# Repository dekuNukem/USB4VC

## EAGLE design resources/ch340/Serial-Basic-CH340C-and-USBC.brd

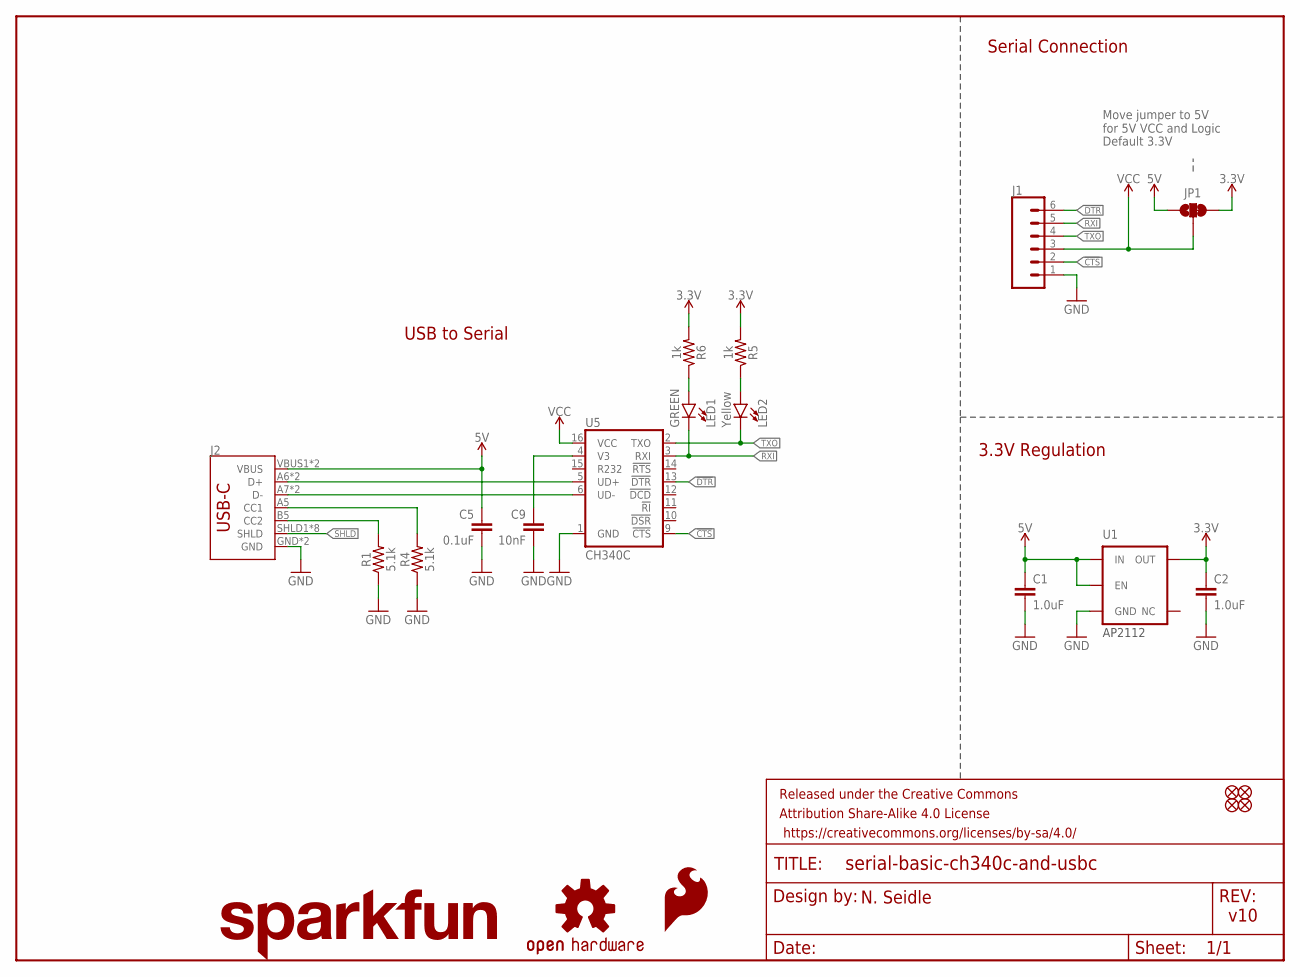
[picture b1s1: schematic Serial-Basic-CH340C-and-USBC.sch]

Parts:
C1, C2: 1.0uF; 0603
C5: 0.1uF; 0603
C9: 10nF; 0603
FRAME1: FRAME-LETTER; CREATIVE_COMMONS
J1: CONN_06SMD-FEMALE-V2; 1X06-SMD-FEMALE
J2: USB_C16PIN; USB-C-16P
JP1: JUMPER-SMT_3_1-NC_TRACE_SILK; SMT-JUMPER_3_1-NC_TRACE_SILK
JP3, JP4, JP5, JP6: FIDUCIAL1X2; FIDUCIAL-1X2
LED1: GREEN; LED-0603
LED2: Yellow; LED-0603
LOGO1: OSHW-LOGOS; OSHW-LOGO-S
LOGO2: SFE_LOGO_FLAME.1_INCH; SFE_LOGO_FLAME_.1
LOGO3: SFE_LOGO_NAME.1_INCH; SFE_LOGO_NAME_.1
R1, R4: 5.1k; 0603
R5, R6: 1k; 0603
U1: 3.3V; SOT23-5
U5: CH340C; SO016

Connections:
3.3V: C2.1, JP1.3, R5.2, R6.2, U1.5 (OUT)
5V: C1.1, C5.1, J2.VBUS1 (VBUS), J2.VBUS2 (VBUS), JP1.1, U1.1 (IN), U1.3 (EN)
!CTS: J1.2, U5.9 (!CTS)
!DTR: J1.6, U5.13 (!DTR)
CC1: J2.A5 (CC1), R4.2
CC2: J2.B5 (CC2), R1.2
D+: J2.A6 (D+), J2.B6 (D+), U5.5 (UD+)
D-: J2.A7 (D-), J2.B7 (D-), U5.6 (UD-)
GND: C1.2, C2.2, C5.2, C9.2, J1.1, J2.GND, J2.GND2 (GND), R1.1, R4.1, U1.2 (GND), U5.1 (GND)
unnamed: C9.1, U5.4 (V3)
unnamed: LED1.A, R6.1
unnamed: LED2.A, R5.1
RXI: J1.5, LED1.C, U5.3 (RXI)
SHLD: J2.SHLD1 (SHLD), J2.SHLD2 (SHLD), J2.SHLD3 (SHLD), J2.SHLD4 (SHLD), J2.SHLD5 (SHLD), J2.SHLD6 (SHLD), J2.SHLD7 (SHLD), J2.SHLD8 (SHLD)
TXO: J1.4, LED2.C, U5.2 (TXO)
VCC: J1.3, JP1.2, U5.16 (VCC)

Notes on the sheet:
Default 3.3V
v10
USB to Serial
3.3V Regulation
N. Seidle
Move jumper to 5V for 5V VCC and Logic
Serial Connection
AP2112

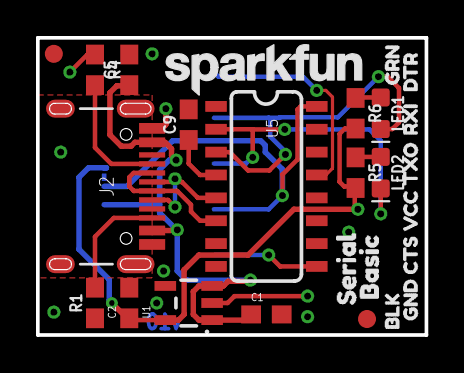
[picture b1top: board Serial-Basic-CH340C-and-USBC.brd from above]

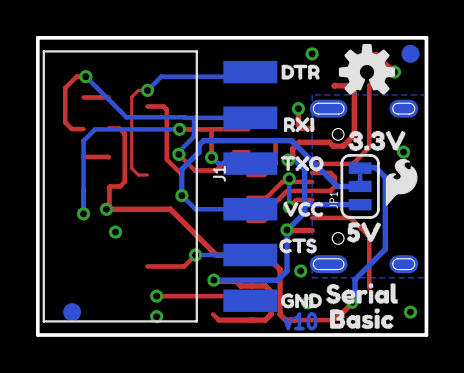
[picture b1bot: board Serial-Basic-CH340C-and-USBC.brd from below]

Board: 2 copper layers, 21.6 x 16.5 mm, 43 parts (16 on the bottom side), 16 nets.

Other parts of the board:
U$1, U$14: CTS1
U$2: 3#3V8
U$3: 5V9
U$4, U$9: SERIAL0
U$5, U$12: TXO0
U$6, U$13: VCC2
U$7, U$11: BASIC1
U$8, U$18: DTR0
U$10, U$21: RXI1
U$15, U$19: GND5
U$17: BLK6
U$20: GRN7

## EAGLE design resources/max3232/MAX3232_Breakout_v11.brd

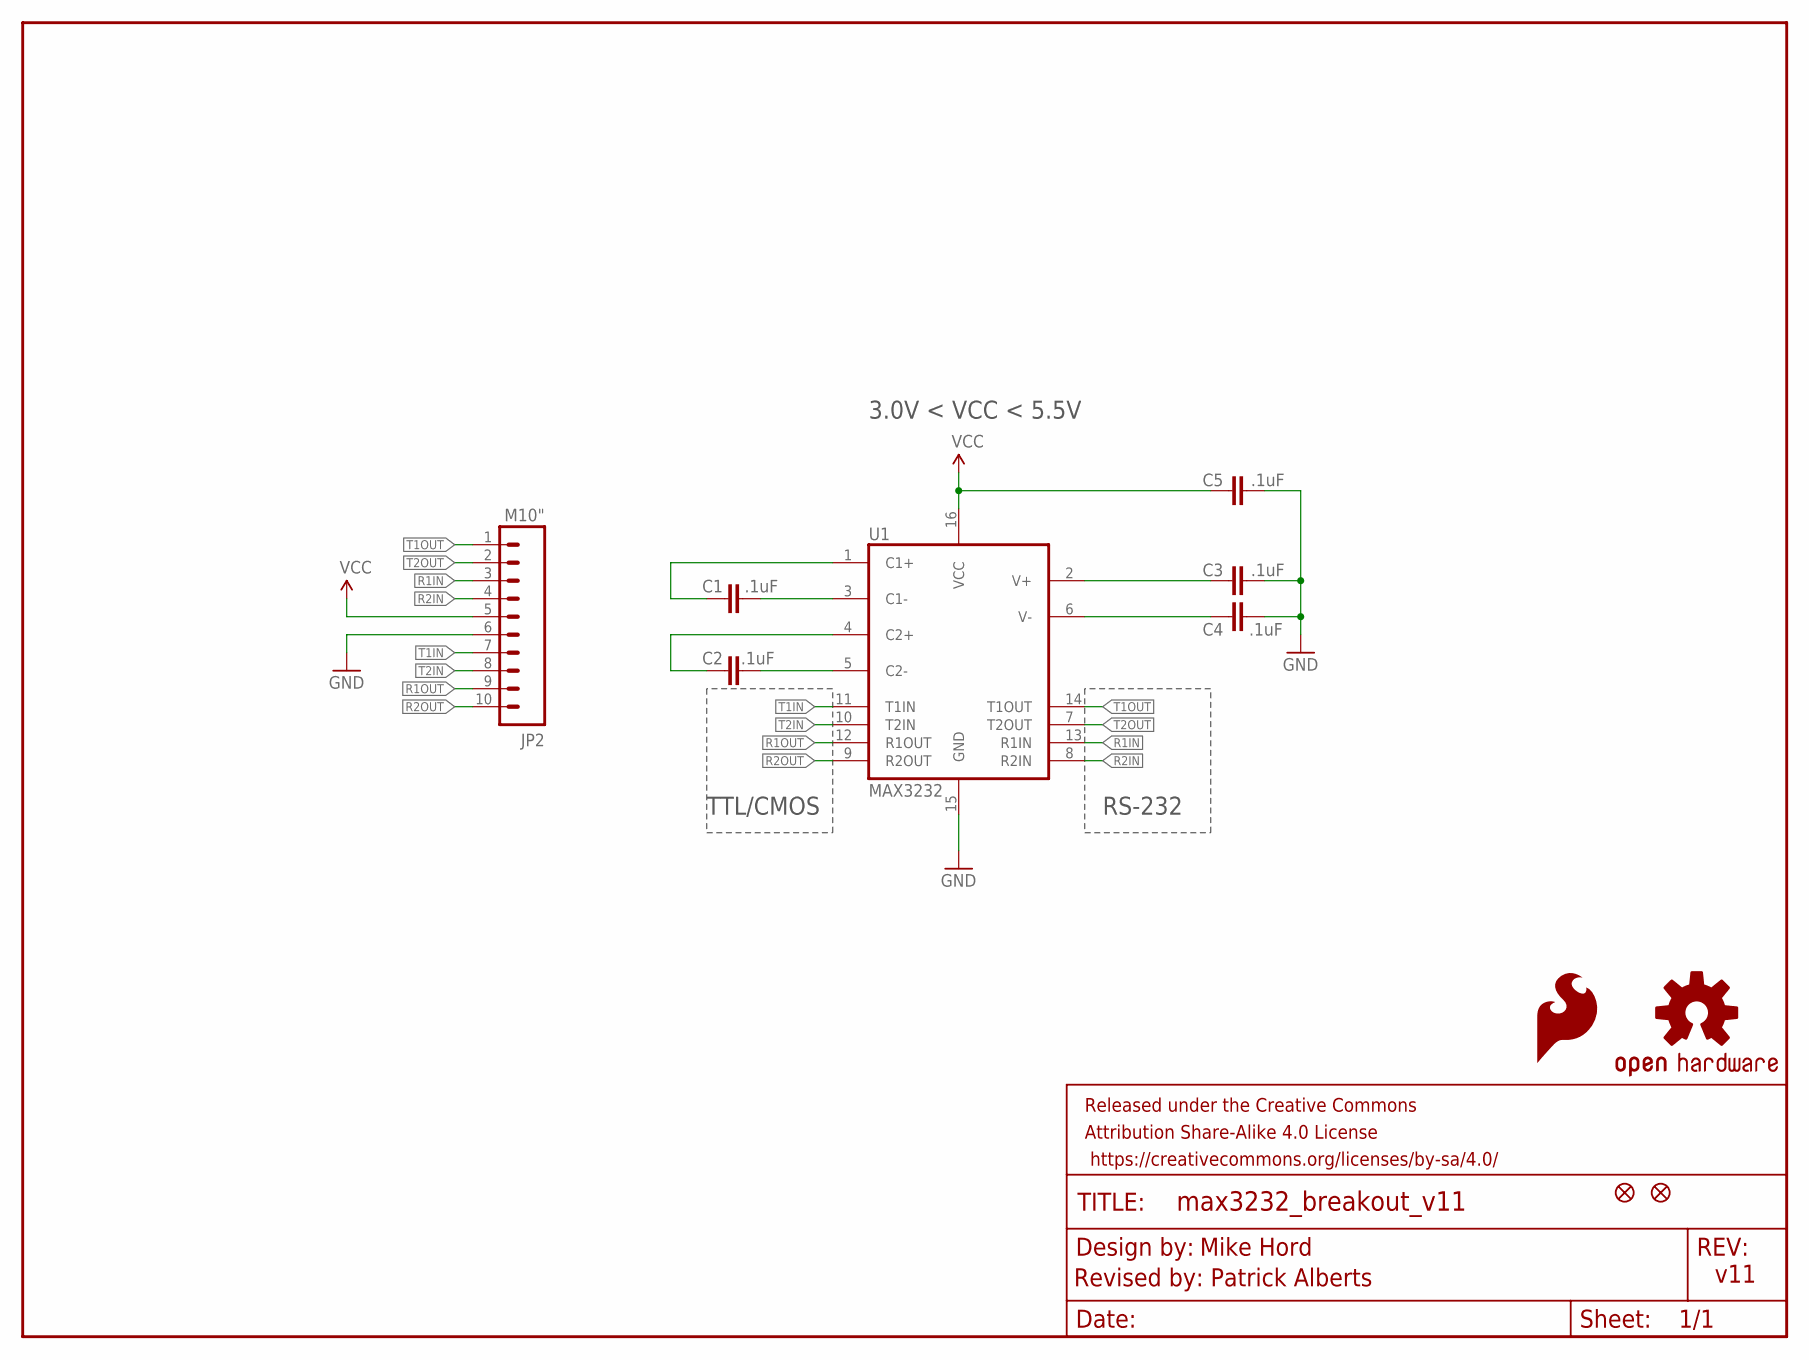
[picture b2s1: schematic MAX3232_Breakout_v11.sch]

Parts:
C1, C2, C3, C4, C5: .1uF; 0603-CAP
FID1, FID2: FIDUCIAL1X2; FIDUCIAL-1X2
FRAME1: FRAME-LETTER; CREATIVE_COMMONS
JP2: M10"; 1X10
LOGO1: SFE_LOGO_FLAME.1_INCH; SFE_LOGO_FLAME_.1
U1: MAX3232; SO016
U$1: OSHW-LOGOS; OSHW-LOGO-S

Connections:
C1+: C1.1, U1.1 (C1+)
C1-: C1.2, U1.3 (C1-)
C2+: C2.1, U1.4 (C2+)
C2-: C2.2, U1.5 (C2-)
GND: C3.2, C4.2, C5.2, JP2.6, U1.15 (GND)
R1IN: JP2.3, U1.13 (R1IN)
R1OUT: JP2.9, U1.12 (R1OUT)
R2IN: JP2.4, U1.8 (R2IN)
R2OUT: JP2.10, U1.9 (R2OUT)
T1IN: JP2.7, U1.11 (T1IN)
T1OUT: JP2.1, U1.14 (T1OUT)
T2IN: JP2.8, U1.10 (T2IN)
T2OUT: JP2.2, U1.7 (T2OUT)
V+: C3.1, U1.2 (V+)
V-: C4.1, U1.6 (V-)
VCC: C5.1, JP2.5, U1.16 (VCC)

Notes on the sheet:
RS-232
TTL/CMOS
3.0V < VCC < 5.5V
Mike Hord
Revised by: Patrick Alberts
v11

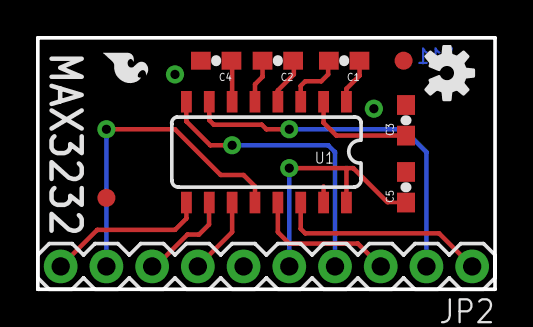
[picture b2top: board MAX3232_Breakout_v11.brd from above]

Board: 2 copper layers, 25.4 x 14.0 mm, 12 parts (0 on the bottom side), 16 nets.

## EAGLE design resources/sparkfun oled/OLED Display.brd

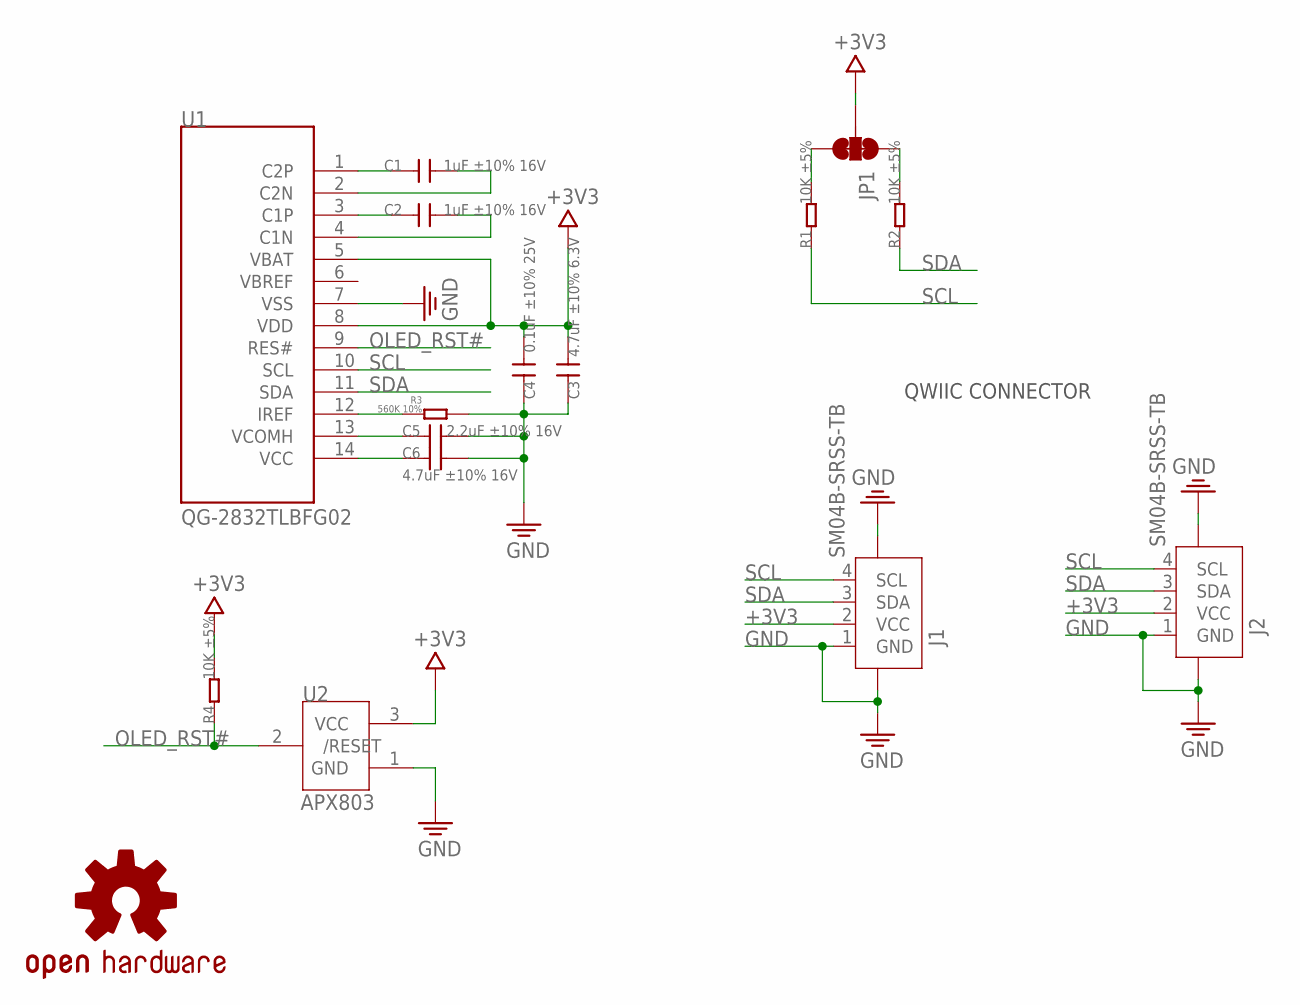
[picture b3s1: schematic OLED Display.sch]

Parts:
C1, C2: 1uF ±10% 16V; 0603
C3: 4.7uF ±10% 6.3V; 0603
C4: 0.1uF ±10% 25V; 0603
C5: 2.2uF ±10% 16V; 0603
C6: 4.7uF ±10% 16V; 0603
J1, J2: SM04B-SRSS-TB; JST-SH-4P
JP1: SMT-JUMPER_3_2-NC_TRACE
LOGO2: OSHW-LOGOMINI; OSHW-LOGO-MINI
R1, R2, R4: 10K ±5%; 0603
R3: 560K 10%; 0603
U1: QG-2832TLBFG02; OLED-12832
U2: APX803; SOT23

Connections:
+3V3: C3.1, C4.1, J1.2 (VCC), J2.2 (VCC), JP1.2, R4.2, U1.5 (VBAT), U1.8 (VDD), U2.3 (VCC)
GND: C3.2, C4.2, C5.2, C6.2, J1.1 (GND), J1.NC1 (5), J1.NC2 (6), J2.1 (GND), J2.NC1 (5), J2.NC2 (6), R3.1, U1.7 (VSS), U2.1 (GND)
unnamed: C1.2, U1.1 (C2P)
unnamed: C1.1, U1.2 (C2N)
unnamed: C2.2, U1.3 (C1P)
unnamed: C2.1, U1.4 (C1N)
unnamed: JP1.3, R1.2
unnamed: C5.1, U1.13 (VCOMH)
unnamed: C6.1, U1.14 (VCC)
unnamed: JP1.1, R2.2
unnamed: R3.2, U1.12 (IREF)
OLED_RST#: R4.1, U1.9 (RES#), U2.2 (/RESET)
SCL: J1.4 (SCL), J2.4 (SCL), R1.1, U1.10 (SCL)
SDA: J1.3 (SDA), J2.3 (SDA), R2.1, U1.11 (SDA)

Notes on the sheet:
QWIIC CONNECTOR

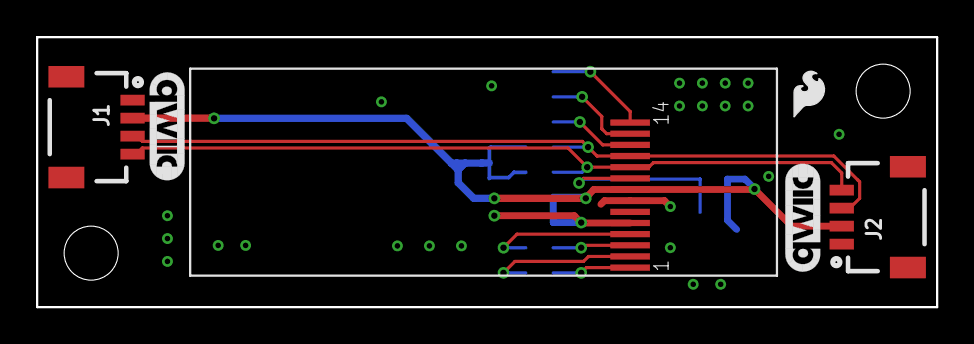
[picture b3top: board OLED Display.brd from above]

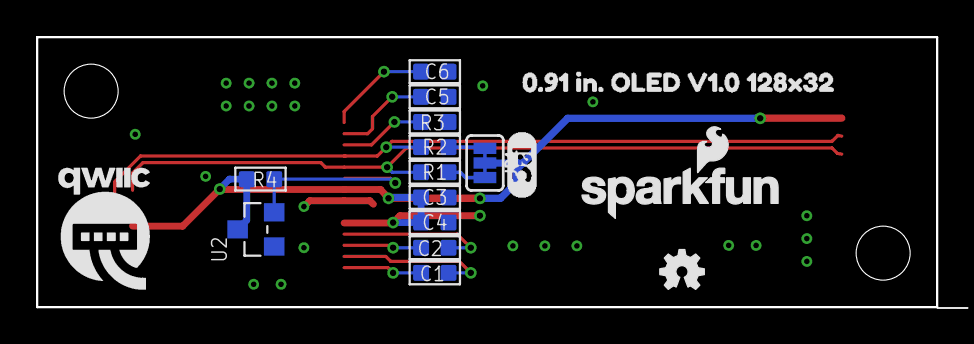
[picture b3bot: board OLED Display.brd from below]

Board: 2 copper layers, 50.0 x 15.0 mm, 23 parts (17 on the bottom side), 14 nets.

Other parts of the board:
U$6: QWIIC-LOGO-MEDIUM
U$7: 0#91_IN#_OLED_V1#0_128X320
U$8: SFE_LOGO_FLAME_.1
U$9: SFE_LOGO_NAME_FLAME_.1
U$11, U$12: QWIIC_6MM
U$20: I_SUPER2_C-()-04

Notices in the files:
parts and their libraries:
SparkFun-Aesthetics: Licensing: CC v3.0 Share-Alike You are welcome to use this library for commercial purposes.
SparkFun-Aesthetics: Released under the Creative Commons Attribution Share-Alike 4.0 License
SparkFun-Aesthetics: https://creativecommons.org/licenses/by-sa/4.0
